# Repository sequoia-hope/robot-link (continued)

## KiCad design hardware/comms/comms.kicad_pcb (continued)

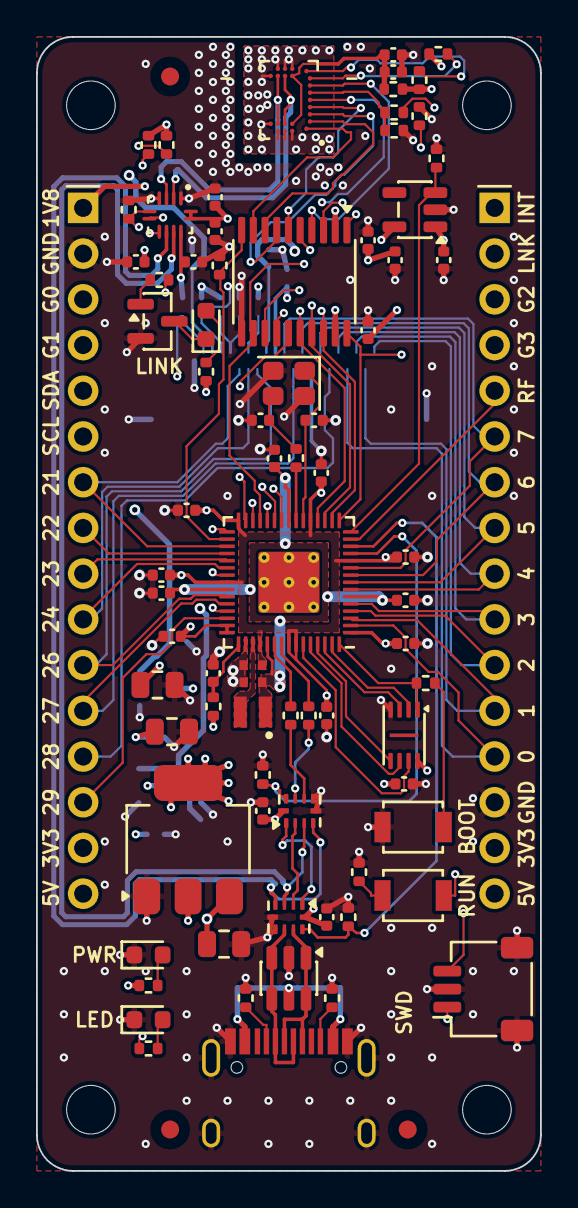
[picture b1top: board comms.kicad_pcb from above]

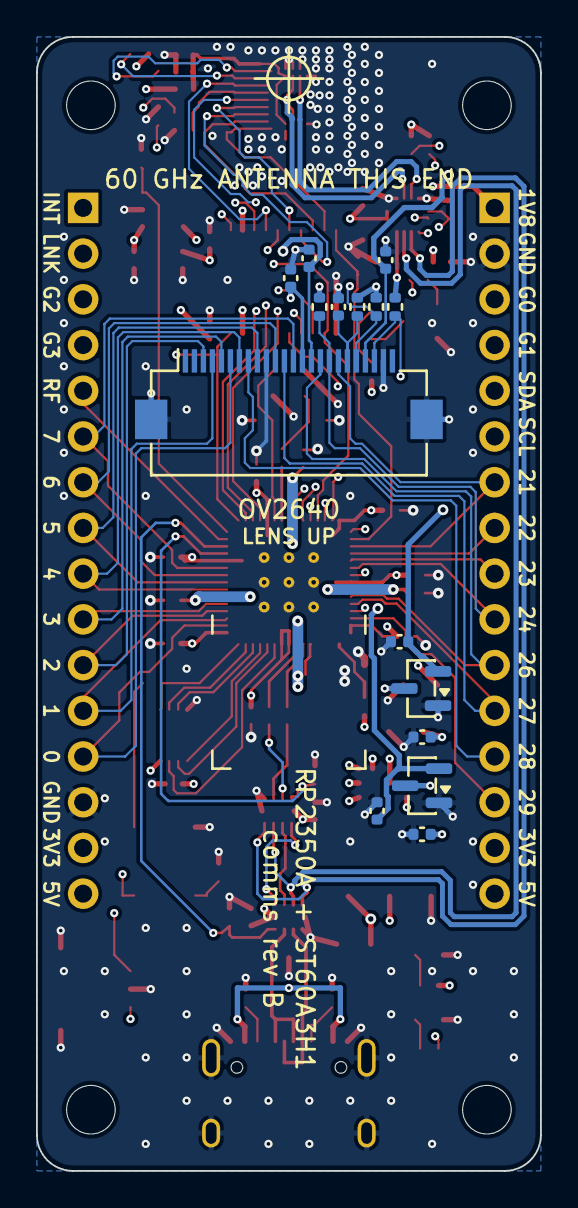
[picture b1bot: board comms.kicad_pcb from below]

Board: 6 copper layers, 28.0 x 63.0 mm, 100 parts (15 on the bottom side), 83 nets.

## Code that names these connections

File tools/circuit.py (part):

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
# The RP2350's GPIO. The chip sits turned half round, so that its USB and
# QSPI side faces the USB-C connector at the bottom edge and the side with
# GPIO12-18 faces the translator. Every signal leaves the chip on the side
# it is wanted: what goes to the ST60 from the top, what goes to the bottom
# of the board from the bottom of a side, the rest straight out to a header.
#
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    9: "USB_SEL_CONN",   # high: the USB-C connector goes to the eUSB2 repeater
    10: "RF_EN_GP",      # RF_EN, through the divider to 1.8 V
    11: "ST_PWR_EN",     # high: the 1.8 V regulator on. Low, or not driven: off (a cold reset of the ST60)
    12: "TUN_G3",        # I2C0 SDA <-> ST60 GPIO[3], the tunnelled SDA
    13: "TUN_G2",        # I2C0 SCL <-> ST60 GPIO[2], the tunnelled SCL
    14: "ST_LINK",       # LINK_STATUS
    15: "ST_INT",        # MODE_INT
    16: "TUN_G0",        # UART0 TX -> ST60 GPIO[0], the tunnelled TXD
    17: "TUN_G1",        # UART0 RX <- ST60 GPIO[1], the tunnelled RXD
    18: "CFG_SDA",       # I2C1: the ST60's configuration port (0x60) and the
    19: "CFG_SCL",       #   PTN3222's (0x43)
    20: "LS_OE",         # the translator's output enable
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                      ("57", "QSPI_SD0"), ("58", "QSPI_SD2"),
                      ("59", "QSPI_SD1"), ("60", "QSPI_SS")):
        cpu[pin] = name
    # GPIO0..29 land on pins 2..5, 7..10, 12..19, 27..29, 31..37, 40..43
    order = [2, 3, 4, 5, 7, 8, 9, 10, 12, 13, 14, 15, 16, 17, 18, 19,
             27, 28, 29, 31, 32, 33, 34, 35, 36, 37, 40, 41, 42, 43]
    for g, pin in zip(range(30), order):
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        {"1": "SWCLK", "2": "GND", "3": "SWDIO", "MP": "GND"}, "debug",
        "Raspberry Pi debug connector: SWCLK, GND, SWDIO")

    add("D3", LED, "blue", FP_LED, {"1": "GND", "2": "LED_A"}, "LED", "user LED, GPIO25")
    add("R9", R, "220R", FP_R["0402"], {"1": "LED", "2": "LED_A"}, "LED", "LED series (Vf 3.1 V)")

    # The headers, 0.9 inch apart. Each runs in the order the chip's pins
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          "GP4", "GP3", "GP2", "GP1", "GP0", "GND", "+3V3", "VBUS"]
    add("J2", "Connector_Generic:Conn_01x16", "LEFT", FP_HDR,
        {str(i + 1): n for i, n in enumerate(j2)}, "headers",
        "tunnelled UART, configuration bus, GPIO21-24 and the ADC pins, rails")
    add("J3", "Connector_Generic:Conn_01x16", "RIGHT", FP_HDR,
        {str(i + 1): n for i, n in enumerate(j3)}, "headers",
        "link status and interrupt, tunnelled I2C, RF_EN, GPIO0-7, rails")
    return out


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    add("C43", C, "1u", FP_C["0402"], {"1": "CAM_RST", "2": "GND"}, "camera",
        "RESET held low through power-up: 10 ms, where OmniVision asks for 3")
    add("R43", R, "10k", FP_R["0402"], {"1": "GP24", "2": "+3V3"}, "camera",
        "PWDN pull-up: the camera sleeps until GPIO24 goes low")
    return out


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
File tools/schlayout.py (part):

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    s.wire((89, 29), s["R7"]["2"])
    s.wire((90, 32), s["R8"]["2"])
    s.wire(s["R7"]["1"], (98, 29))
    s.label(s.g(98, 29), "USB_DP", stub=0, d=(1, 0))
    s.wire(s["R8"]["1"], (98, 32))
    s.label(s.g(98, 32), "USB_DM", stub=0, d=(1, 0))
    for p in u.pins.values():
        if p.d == (1, 0) and p.net and p.num not in ("52", "51"):
            s.label(p, stub=2)
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    for n in ("6", "5", "2", "3", "7"):
        s.label(f[n], stub=2)
    s.wire(f["1"], (11, 41))
    s.label(s.g(11, 41), "QSPI_SS", stub=0, d=(-1, 0))
    s.place("R6", 13, 39.5, rot=180, fields="left")
    s.label(s["R6"]["2"], stub=1, d=(0, -1), text_dir=(1, 0))
    s.wire(f["8"], (19, 37), (22, 37))
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    s.block("Link LED", 46, 54, 96, 73)
    s.place("R29", 62, 66, rot=90, fields="above")
    s.wire(s["R29"]["1"], (54, 66))
    s.label(s.g(54, 66), "ST_LINK_STATUS", stub=0, d=(-1, 0))
    s.place("R23", 57, 67.5, fields="right")
    q1 = s.place("Q1", 67.5, 66, fields=(2.5, 0, "left"))
    s.wire(s["R29"]["2"], q1["1"])
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    # each data pad appears twice on the connector (A and B rows)
    s.wire(j["A7"], (29, 39))
    s.wire(j["B7"], (28, 40), (28, 39))
    s.label(s.g(29, 39), "USB_CONN_DM", stub=0, d=(1, 0))
    s.wire(j["A6"], (29, 41))
    s.wire(j["B6"], (28, 42), (28, 41))
    s.label(s.g(29, 41), "USB_CONN_DP", stub=0, d=(1, 0))
    s.label(j["A5"], stub=1)
    s.label(j["B5"], stub=1)
    s.wire(j["S1"], (17, 50), (23, 50))
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    s.place("C32", 90, 75.5, fields="left")
    s.place("R15", 96, 82, rot=180, fields="right")
    s.wire(s["R15"]["2"], (99, 80.5), (99, 75), v["3"])
    s.label(s.g(96, 80.5), "ST_PWR_EN", stub=1, d=(-1, 0))
    s.wire(v["5"], (116, 74))
    s.place("C33", 112, 75.5, fields="right")
    s.power(s.g(116, 74), "+1V8")
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    r = s.place("R42", 46, 74.5, rot=180, fields="right")
    c = s.place("C43", 46, 79.5, fields="right")
    s.wire(r["1"], c["1"])
    s.label(s.g(46, 77), "CAM_RST", stub=1, d=(-1, 0))

    for ref, cin, cout, y, title in (("U11", "C40", "C41", 28, "2.8 V, the sensor's analogue supply"),
                                     ("U12", "C44", "C42", 58, "1.3 V, the sensor's core")):
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
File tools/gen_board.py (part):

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

def select_copper(B):
    """The two USB path selects, from GPIO8 and GPIO9 at the RP2350's upper
    right to the switches at the bottom of the board. Between lie the
    right-hand header's fan-out and the QSPI bus, all on the front; so both
    go on the back: a via each in the open corner above C15, down the board
    between the chip's ground vias and the header, and across."""
    P = B.pad
    w = 0.15
    p_m, p_c = P("U1", "12"), P("U1", "13")                 # GPIO8, GPIO9
    r13, s_m = P("R13", "1"), P("U10", "9")
    r12, s_c = P("R12", "1"), P("U9", "9")
    xm, xc = 7.1, 8.2             # the two lanes down the back, either side of the RP2350's ground vias
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    turns in toward the connector, the track nearest the centre turning
    first, which keeps the order. The connector's pads can be come at from
    either end: from above, where the module's tail goes in, or from below,
    under the connector's body. The right-hand column splits: GPIO0 and 1
    go in under the body, 2 to 7 go round the end of the pad row and come
    down onto the pads from above. On the left all five go under the body.
    That only works for one order of signals on the pins, and the GPIO map
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    Above the row, at its left-hand end, are the pull-ups, each joined to
    its pad; the two regulated supplies leave between them, each to a via
    the router takes it on from, and the 3.3 V pin goes to a via into its
    plane. SIOD and SIOC (GPIO22/23) are left to the router from there.
    """
    P = B.pad
    w, p = CAM_W, CAM_PITCH
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    def run(net, pts):
        B.track(net, "B.Cu", pts, w)

    # -- right: GPIO0..7 on J3. Columns from x = 8.5 outward, in pin order
    # (8.2 is the USB select's lane).
    hdr = header("J3")
    col = {g: 8.5 + g * p for g in range(8)}
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        px, yh = pad_x(f"GP{g}"), top - 0.65 - (g - 2) * p
        run(f"GP{g}", start(g) + [(col[g], yh + 0.3), (col[g] - 0.3, yh), (px + 0.3, yh), (px, yh + 0.3), (px, top)])

    # -- left: GPIO21, 24, 26, 27, 28 on J2. 28 to 24 gather into a column;
    # 21 is the top pin and crosses first. They run in under the connector
    # together, rise to five lanes below its mounting pad, and each leaves
    # for its pad where the ground vias that come through from the crystal
    # and the 1V1 via from the RP2350 let it: (lane, where it turns up,
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    B.circle("B.SilkS", px, py, 1.2, 0.15)
    B.line("B.SilkS", px - 1.9, py, px + 1.9, py, 0.15)
    B.line("B.SilkS", px, max(0.6, py - 1.9), px, py + 1.9, 0.15)
    for label, x, y, rot in (("BOOT", 9.9, PL.PLACE["SW1"][1], 90), ("RUN", 9.9, PL.PLACE["SW2"][1], 90),
                             ("PWR", -10.8, PL.PLACE["D1"][1], 0), ("LED", -10.8, PL.PLACE["D3"][1], 0),
                             ("LINK", -7.2, 18.3, 0), ("SWD", 6.4, 54.2, 90)):
        B.text("F.SilkS", label, x, y, 0.8, rot=rot, thick=0.15)
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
